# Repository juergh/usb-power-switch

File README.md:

This is a simple circuitry to switch 5V USB power. It is intended to be used
for controlling power of a Raspberry Pi via a GPIO from another Raspberry Pi.

The PWA is designed to fit into a cable like this one.

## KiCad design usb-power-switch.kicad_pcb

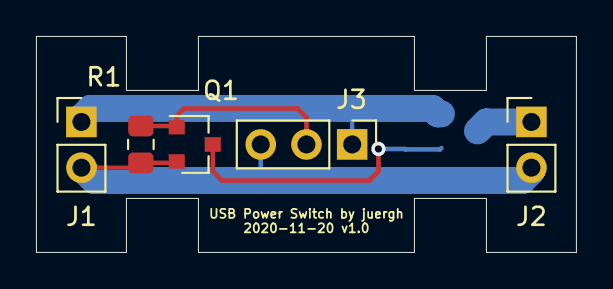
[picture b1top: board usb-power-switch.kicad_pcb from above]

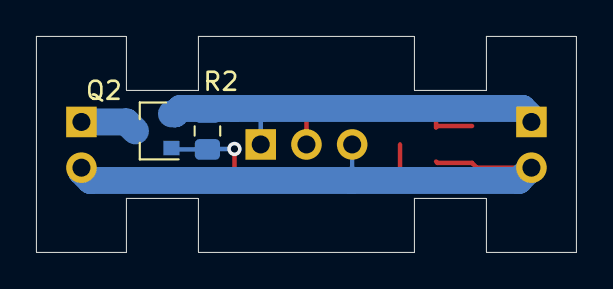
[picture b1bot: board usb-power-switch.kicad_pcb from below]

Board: 2 copper layers, 30.0 x 12.0 mm, 7 parts (2 on the bottom side), 5 nets.

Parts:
J1, J2: Conn_01x02; PinHeader_1x02_P2.54mm_Vertical
J3: Conn_01x03; PinHeader_1x03_P2.54mm_Vertical
Q1: Q_NMOS_GSD; SOT-23
Q2: Q_PMOS_GSD; SOT-23
R1, R2: 10K; R_0805_2012Metric_Pad1.15x1.40mm_HandSolder

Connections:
/Enable: J3.2, Q1.1, R1.1
/Vin: J1.1, J3.1, Q2.2, R2.1
/Vout: J2.1, Q2.3
GND: J1.2, J2.2, J3.3, Q1.2, R1.2
unnamed: Q1.3, Q2.1, R2.2

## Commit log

2020-12-10 Add README.md
